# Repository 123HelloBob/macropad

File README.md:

This is a repo for my project. Currently it's very similar to the example.

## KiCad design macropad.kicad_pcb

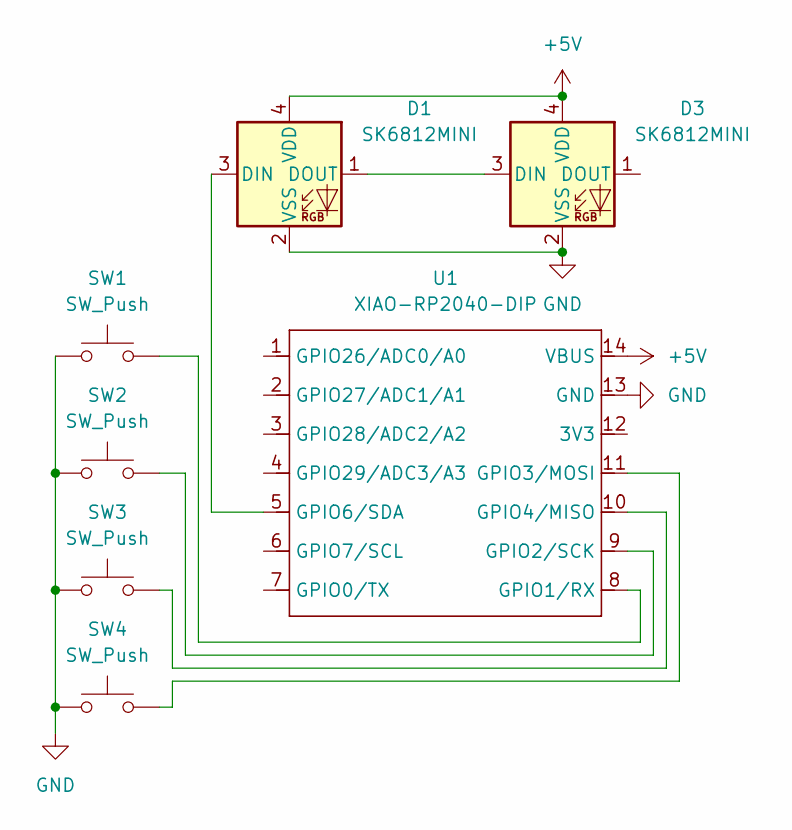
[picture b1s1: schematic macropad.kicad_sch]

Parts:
D1, D3: SK6812MINI; LED_SK6812MINI_PLCC4_3.5x3.5mm_P1.75mm
SW1, SW2, SW3, SW4: SW_Push; SW_Cherry_MX_1.00u_PCB
U1: XIAO-RP2040-DIP

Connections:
+5V: D1.4 (VDD), D3.4 (VDD), U1.14 (VBUS)
GND: D1.2 (VSS), D3.2 (VSS), SW1.1, SW2.1, SW3.1, SW4.1, U1.13 (GND)
unnamed: D1.3 (DIN), U1.5 (GPIO6/SDA)
unnamed: D1.1 (DOUT), D3.3 (DIN)
unnamed: SW1.2, U1.8 (GPIO1/RX)
unnamed: SW2.2, U1.9 (GPIO2/SCK)
unnamed: SW4.2, U1.11 (GPIO3/MOSI)
unnamed: SW3.2, U1.10 (GPIO4/MISO)

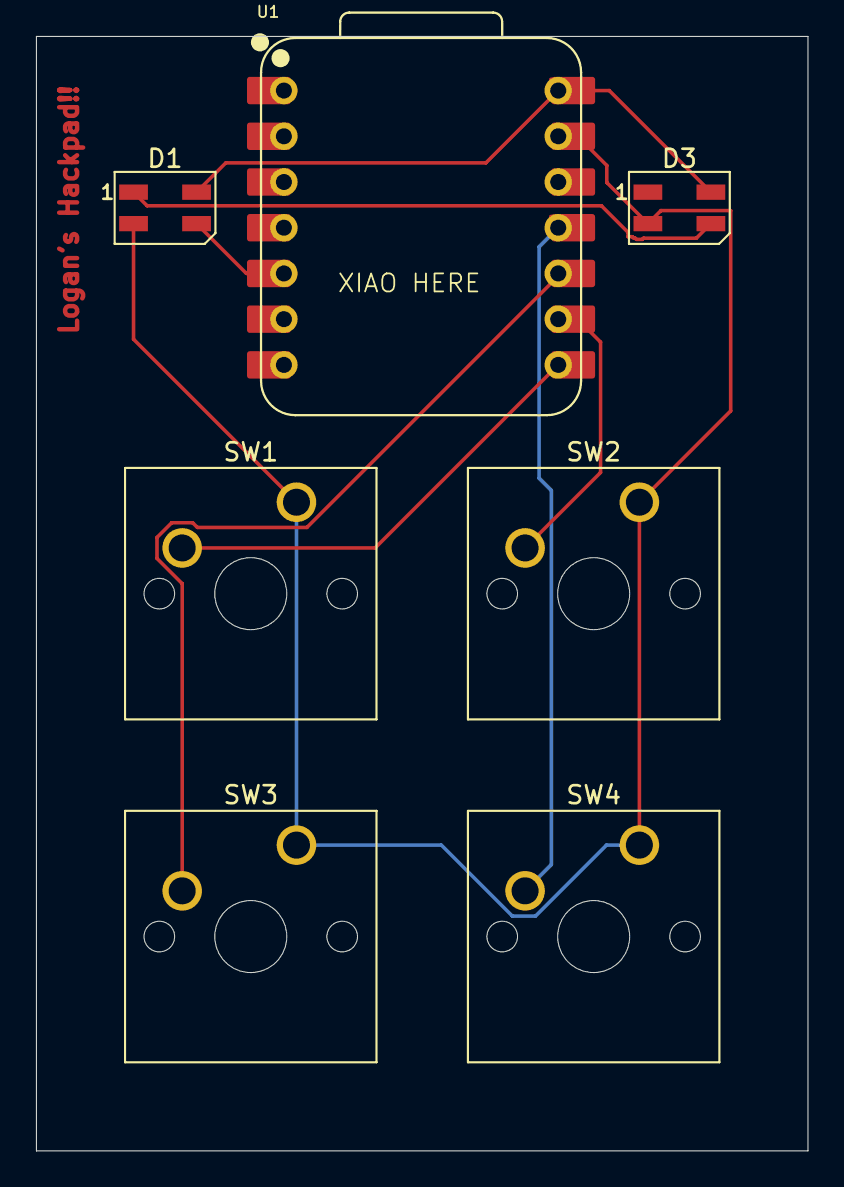
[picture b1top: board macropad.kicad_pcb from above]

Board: 2 copper layers, 42.9 x 61.9 mm, 7 parts (0 on the bottom side), 8 nets.

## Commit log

2025-11-19 Add initial project description to README
2025-11-19 Initialize keyboard firmware with macros and pins
2025-11-21 Macropad files
